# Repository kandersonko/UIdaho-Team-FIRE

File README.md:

# Team FIRE GitHub
## University of Idaho
### Collin Heist, Shelby Linafelter, and Koffi Anderson

## Existing Files

-  `/Component Test Board/`
	* This directory is for the _KiCad_ project dedicated to the __Component Test Board__.

- `/Board Redesign/`
	* This directory is for the _KiCad_ project dedicated to the __IRIDIUM 9523 carrier redesign__.
	* Within this is __Iridium Carrier (2). *__ files. These files are the Eagle project files, and the previous Senior Design Team's (Team SCUBEE) schematic and PCB files being used for reference.
	* The redesigned project is being placed within `/KiCad Project/`, and this directory contains the Eeschema and PCBnew footprints and symbols created for the purpose of this board.
	
## To Do

- Find a replacement for the LT3959 Boost circuit
- Verify the final status of `JP4` (Sim Card Enable); whether it is tied to the 5V line or the SIM enable line coming from the IRIDIUM 9523
- Verify the status of `JP1` (mode switch pin of IRIDIUM) if it's tied to GND or to the status of `JP2`.
- Verify the status of `JP2` (mode switch high-voltage jumper); if it is tied to 3.3V ISENSE line or 3.3V bus.
- Verify the status of `JP3` (RF enable reference voltage); if it is tied to 3.3V ISENSE line or 3.3V bus.
- Determine whether `S1` (the RF enable switch?) is necessary in end-product.
- Verify the status of `JP5` (the VCCA power source of `U3`); is it tied to 3.3V ISENSE or 3.3V bus.
- Determine if `JP3` (the +3.3V, +5V, and bus power voltage 3-pin header) is required in end-product.
- Decided whether the SAMD21 is adequate, or should we transition over to the SAMD51 for memory / I2C capabilities.
- Determine whether `S2` (the microcontroller reset switch) is necessary in the final product.
- Identify which test points are essential / desired.

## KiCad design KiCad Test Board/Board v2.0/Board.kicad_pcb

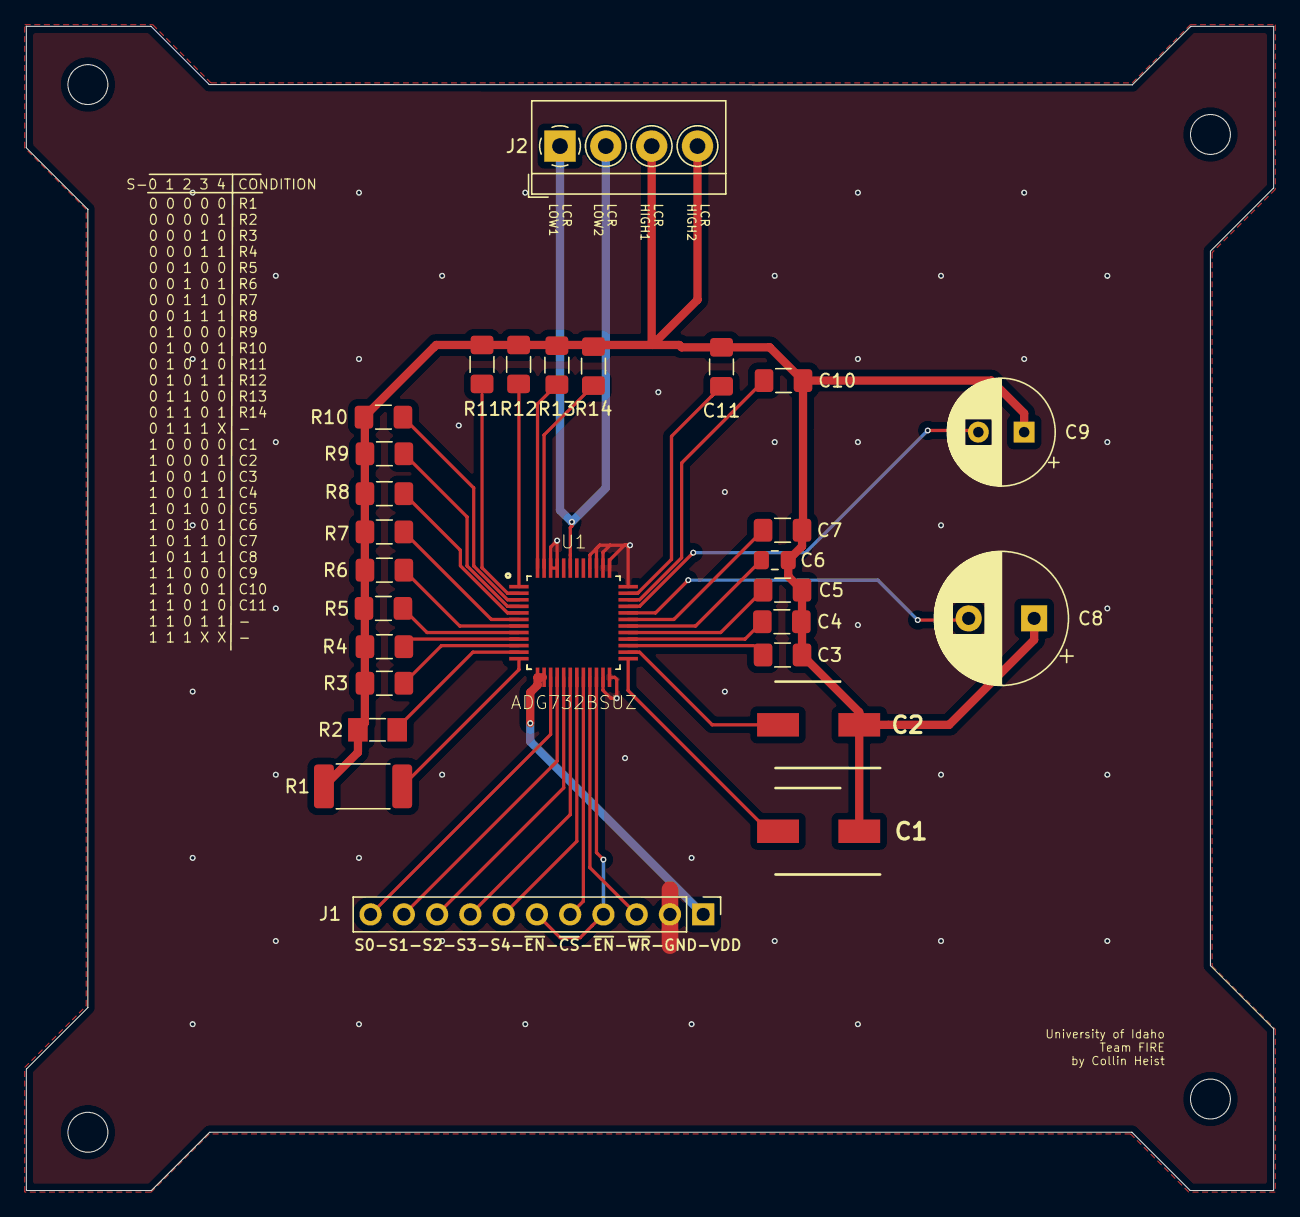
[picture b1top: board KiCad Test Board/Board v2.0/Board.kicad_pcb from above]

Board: 2 copper layers, 95.2 x 88.9 mm, 28 parts (0 on the bottom side), 37 nets.

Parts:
C1, C2: 47u; CAPAE660X640N
C3, C4, C5, C7: 0.1u; C_1206_3216Metric_Pad1.42x1.75mm_HandSolder
C6: 0.1u; C_0805_2012Metric_Pad1.15x1.40mm_HandSolder
C8: 10; CP_Radial_D10.0mm_P5.00mm
C9: 2.2; CP_Radial_D8.0mm_P3.50mm
C10, C11: 47u; C_1206_3216Metric_Pad1.42x1.75mm_HandSolder
J1: Conn_01x11; PinHeader_1x11_P2.54mm_Vertical
J2: Screw_Terminal_01x04; TerminalBlock_4Ucon_1x04_P3.50mm_Horizontal
R1: 1.5k; R_2512_6332Metric_Pad1.52x3.35mm_HandSolder
R2: 1k; R_MiniMELF_MMA-0204
R3, R4, R5: 1k; R_1206_3216Metric_Pad1.42x1.75mm_HandSolder
R6: 20m; R_1206_3216Metric_Pad1.42x1.75mm_HandSolder
R7: 470m; R_1206_3216Metric_Pad1.42x1.75mm_HandSolder
R8: 100; R_1206_3216Metric_Pad1.42x1.75mm_HandSolder
R9, R10, R11, R12, R13, R14: 10k; R_1206_3216Metric_Pad1.42x1.75mm_HandSolder
U1: ADG732BSUZ; QFP50P900X900X120-49N

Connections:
GND: J1.2, U1.23, U1.24, U1.36, U1.37, U1.38, U1.39, U1.40, U1.45, U1.46
LCR_HIGH1: C1.1, C2.1, C3.1, C4.1, C5.1, C6.1, C7.1, C8.1, C9.1, C10.1, C11.1, J2.3, J2.4, R1.2, R2.2, R3.2, R4.2, R5.2, R6.2, R7.2, R8.2, R9.2, R10.2, R11.2, R12.2, R13.2, R14.2
LCR_LOW1: J2.1, J2.2, U1.43
unnamed: C1.2, U1.25
unnamed: C2.2, U1.26
unnamed: C3.2, U1.27
unnamed: C4.2, U1.28
unnamed: C5.2, U1.29
unnamed: C6.2, U1.30
unnamed: C7.2, U1.31
unnamed: C8.2, U1.32
unnamed: C9.2, U1.33
unnamed: C10.2, U1.34
unnamed: C11.2, U1.35
unnamed: R1.1, U1.12
unnamed: R2.1, U1.11
unnamed: R3.1, U1.10
unnamed: R4.1, U1.9
unnamed: R5.1, U1.8
unnamed: R6.1, U1.7
unnamed: R7.1, U1.6
unnamed: R8.1, U1.5
unnamed: R9.1, U1.4
unnamed: R10.1, U1.3
unnamed: R11.1, U1.2
unnamed: R12.1, U1.1
unnamed: R13.1, U1.48
unnamed: R14.1, U1.47
SELECT0: J1.11, U1.15
SELECT1: J1.10, U1.16
SELECT2: J1.9, U1.17
SELECT3: J1.8, U1.18
SELECT4: J1.7, U1.19
VDD: J1.1, U1.13, U1.14
~CS: J1.5, U1.20
~EN: J1.4, J1.6, U1.22
~WR: J1.3, U1.21

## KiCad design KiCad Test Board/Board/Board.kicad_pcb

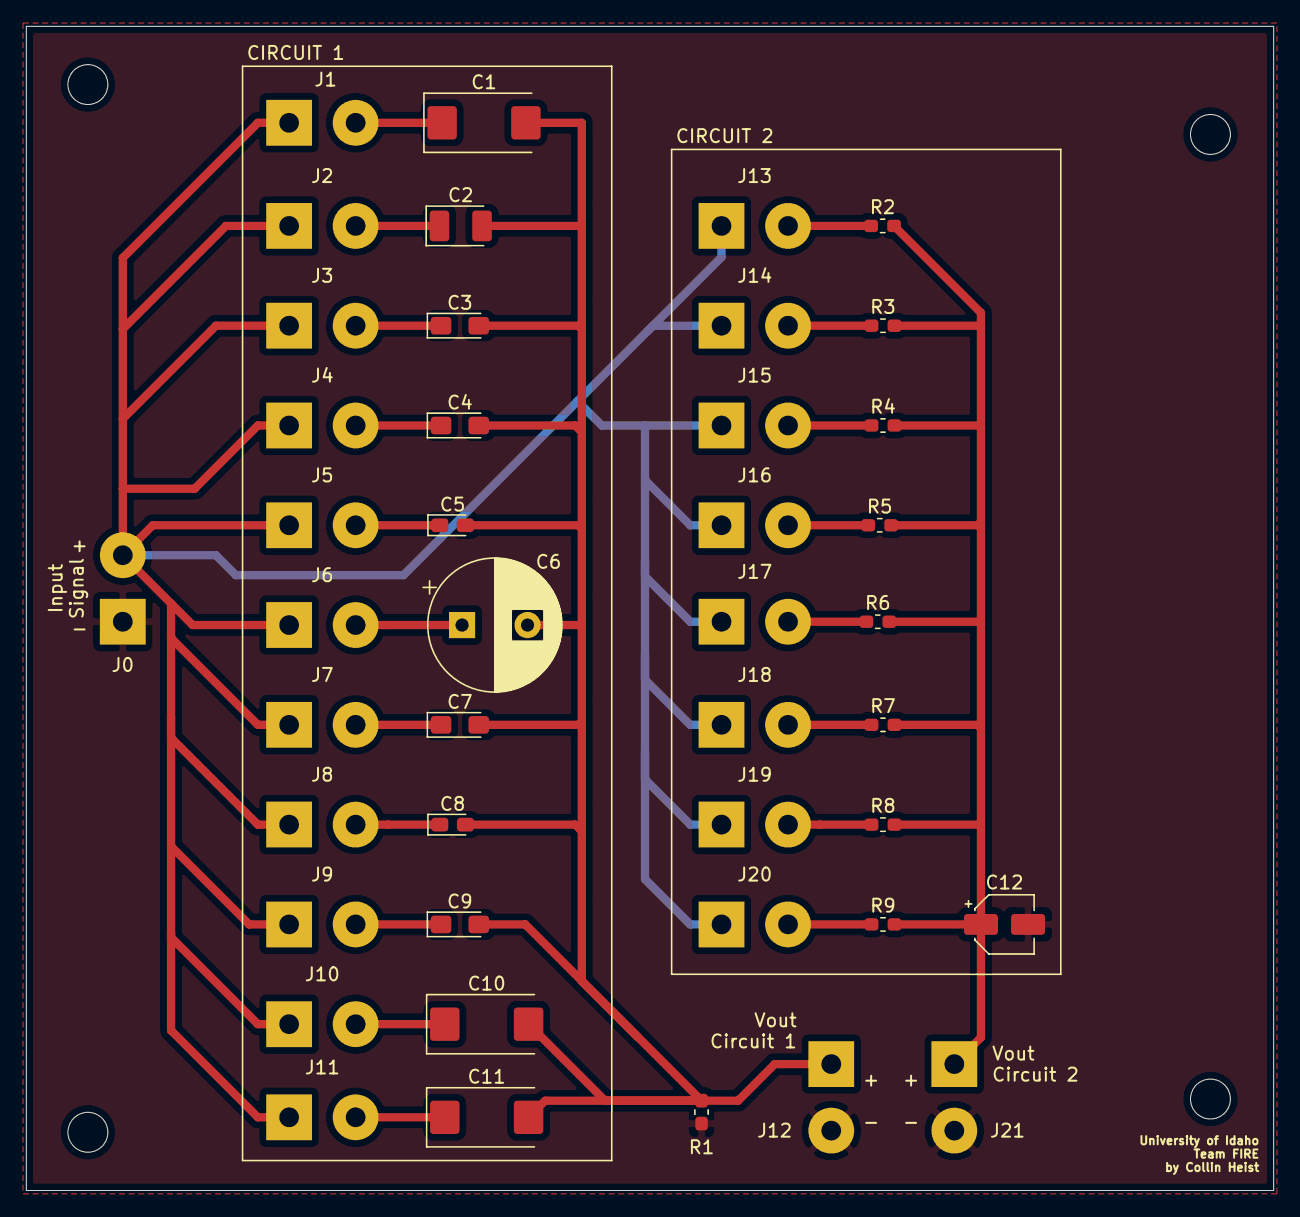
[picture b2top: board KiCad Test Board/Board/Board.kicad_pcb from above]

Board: 2 copper layers, 95.2 x 88.9 mm, 43 parts (0 on the bottom side), 23 nets.

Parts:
C1: 4.7uF; CP_EIA-7343-43_Kemet-X_Pad2.25x2.55mm_HandSolder
C2: 2.2uF; CP_EIA-3528-21_Kemet-B_Pad1.50x2.35mm_HandSolder
C3: 10uF; CP_EIA-3216-18_Kemet-A_Pad1.58x1.35mm_HandSolder
C4: 4.7uF; CP_EIA-3216-18_Kemet-A_Pad1.58x1.35mm_HandSolder
C5: 1uF; CP_EIA-2012-15_AVX-P_Pad1.30x1.05mm_HandSolder
C6: 330uF; CP_Radial_D10.0mm_P5.00mm
C7, C9: 0.22uF; CP_EIA-3216-10_Kemet-I_Pad1.58x1.35mm_HandSolder
C8: 10uF; CP_EIA-2012-12_Kemet-R_Pad1.30x1.05mm_HandSolder
C10, C11: 10uF; CP_EIA-7343-40_Kemet-Y_Pad2.25x2.55mm_HandSolder
C12: 10uF; CP_Elec_4x5.4
J0, J1, J2, J3, J4, J5, J6, J7, J8, J9, J10, J11, J12, J13, J14, J15, J16, J17, J18, J19, J20, J21: Conn_01x02; SolderWirePad_1x02_P5.08mm_Drill1.5mm
R1, R3, R6: 10k; R_0603_1608Metric_Pad1.05x0.95mm_HandSolder
R2: 3.3k; R_0603_1608Metric_Pad1.05x0.95mm_HandSolder
R4: 59k; R_0603_1608Metric_Pad1.05x0.95mm_HandSolder
R5: 1k; R_0603_1608Metric_Pad1.05x0.95mm_HandSolder
R7: 20k; R_0603_1608Metric_Pad1.05x0.95mm_HandSolder
R8: 100k; R_0603_1608Metric_Pad1.05x0.95mm_HandSolder
R9: 330; R_0603_1608Metric_Pad1.05x0.95mm_HandSolder

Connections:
GND: C12.2, J0.1, J12.2, J21.2, R1.2
unnamed: C1.1, J1.2
unnamed: C2.1, J2.2
unnamed: C3.1, J3.2
unnamed: C4.1, J4.2
unnamed: C5.1, J5.2
unnamed: C6.1, J6.2
unnamed: C7.1, J7.2
unnamed: C8.1, J8.2
unnamed: C9.1, J9.2
unnamed: C10.1, J10.2
unnamed: C11.1, J11.2
unnamed: J13.2, R2.1
unnamed: J14.2, R3.1
unnamed: J15.2, R4.1
unnamed: J16.2, R5.1
unnamed: J17.2, R6.1
unnamed: J18.2, R7.1
unnamed: J19.2, R8.1
unnamed: J20.2, R9.1
V_in: J0.2, J1.1, J2.1, J3.1, J4.1, J5.1, J6.1, J7.1, J8.1, J9.1, J10.1, J11.1, J13.1, J14.1, J15.1, J16.1, J17.1, J18.1, J19.1, J20.1
V_out1: C1.2, C2.2, C3.2, C4.2, C5.2, C6.2, C7.2, C8.2, C9.2, C10.2, C11.2, J12.1, R1.1
V_out2: C12.1, J21.1, R2.2, R3.2, R4.2, R5.2, R6.2, R7.2, R8.2, R9.2

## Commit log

2020-01-21 Initial Component Test PCB
    - Added initial component test PCB files
    - Added starting Eagle Project and Schematic files for the IRIDIUM carrier
2020-01-23 Updated KiCad project files
2020-02-09 Started KiCad Version
2020-02-13 Removed untested components
    A bit late; removed unused components from schematic - not PCB
2020-02-14 Added 9523 User Manual
    - Added 9523 User manual
    - Started work on redesign schematic
2020-02-18 Worked more on board!
    - Moved more of the schematic over to KiCad
    - Created models and footprints / symbols for a few components
2020-02-19 Hecho más progreso
    - Added I2C bus converter
    - Added all voltage translators
    - Created hierarchical schematics
2020-02-20 Added I2C Expander
    - Added all required connections for the I2C expander
2020-02-21 Made more progress on board redesign
    - Primarily deleted useless (for our purposes) items from the old schematic so we do not have to spend time transferring them over.
    - Finished some component transfer
    - Renamed some folders
2020-02-21 Added to-do list to README
2020-02-25 Team-FIRE-v2.zip
    Archived project file (sending to new branch w/ pull request because I don't know how to use GitHub properly with these types of files :D)
2020-02-27 Fix: added files to ignore
2020-02-28 Added Shelby's work
2020-02-28 Added changes to SCH1
    - Added Shelby's changes to SCH1
2020-03-05 Deleted problematic file
    Hope this helps, Shelby!
2020-03-05 Try this!
2020-03-05 ...now?
2020-03-05 Now!
2020-03-05 Added SAMD51
    - Created schematic symbol, footprint, and 3D model for the SAMD51
    - Added SAMD51 to the schematic (only partially implemented)
    - Added decoupling capacitors to the 3.3V bus (as recommended by the SAMD51 design manual)
    - Started checklist for SAMD51 implementation on the top-level schematic sheet; there's no convenient breakout board to emulate
    - Implemented power connections for SAMD51
2020-03-10 Added SAMD51 Breakout
2020-03-11 Fix: modified gitignore to fix some files that were tracked
2020-03-11 Add: reset button and some comments
2020-03-11 Add: swclk pin connection for reliability of operation of the SAMD51
2020-03-12 Smol changes
2020-03-12 Add: crystall oscillator and made some updates
2020-03-12 Add: no connection flag for (NC) no connect
2020-03-12 Fix: updated some comments
2020-03-12 Deleted Old Boost...
2020-03-12 Fix: moved some parts
2020-03-12 Fix: added missing wiring to crystal oscillator
2020-04-23 Updated .gitignore
2020-04-23 Finished RF Connector
    - Fixed alignment of schematic sheet 2
    - Crated U.F connector symbol, layout, and 3D symbol
    - Created coax symbol, layout, and 3D symbol
    - Added RF connector to Schematic sheet 3
2020-04-23 Minor label fix on RF connector
    - Removed display of "value" field on RF connector, changed display to MPN on both
2020-04-23 Boost Added
2020-04-24 Added PMIC part, 3.3V lin reg part, and buck converter + testpoint part
2020-04-24 Added BOM
    - Removed .csv from .gitignore
    - Added BOM output
    - Removed graphic from PCB
2020-04-24 Added TES connector
    - Added the two 1x3 connectors to page 3 of the schematic
2020-04-24 Finished RF Connector
    - Deleted old 132136RP antenna connector
    - Added new MMCX antenna connector footprint, symbol, and 3D model
    - Added MMCX antenna and U.FL connector to Schematic Page 3
2020-04-27 Fix: refactor symbol and modified schematics
2020-04-27 Finished PMICs
    - Finished stuff on schematic page 3!
2020-04-27 Progress
    - Corrected many footprint errors on components
    - Finalized work on schematic 3
2020-04-27 Buck Converter & Test Points
2020-04-28 Fix connections
2020-04-28 Update SAMD51
